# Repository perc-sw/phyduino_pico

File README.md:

# Phyduino Pico

## Description

This repository has all CAD files for the Phyduino Pico board used in the University of Toronto, Department of Physic, "[Introduction to Electronics course.](https://perc-sw.github.io/intro_to_electronics/)" 

This board is used to train graduate students first and foremost in surface mount hole solder techniques. As part of the training in the course they will as learn digital interfaces and digital IO design methods as well. This board is a fully function Arduino Uno style board using the Raspberry PI RP2040 microcontroller.

The CAD program used to design this board is [KiCAD](https://www.kicad.org/) which open source and free to use. The [Interactive Html BoM](https://github.com/openscopeproject/InteractiveHtmlBom) plugin was used to generate the interactive bill of materials html file.

## Files

- Gerber Files are located in the [fabrication folder](./fab)
- There is an [Interactive bill of materials html file](https://perc-sw.github.io/phyduino_pico/bom/ibom_student.html) that you can use to assist you in assembling the board. 
- PDF of [Schematic](./docs/pdf/board/phyduino_pico_schematic.pdf)
- PDF of PCB
    - [Top Layer](./docs/pdf/board/phyduino_pico_pcb_front.pdf)
    - [Inner Layer 1](./docs/pdf/board/phyduino_pico_pcb_inner1.pdf)
    - [Inner Layer 2](./docs/pdf/board/phyduino_pico_pcb_inner2.pdf)
    - [Bottom Layer](./docs/pdf/board/phyduino_pico_pcb_back.pdf)

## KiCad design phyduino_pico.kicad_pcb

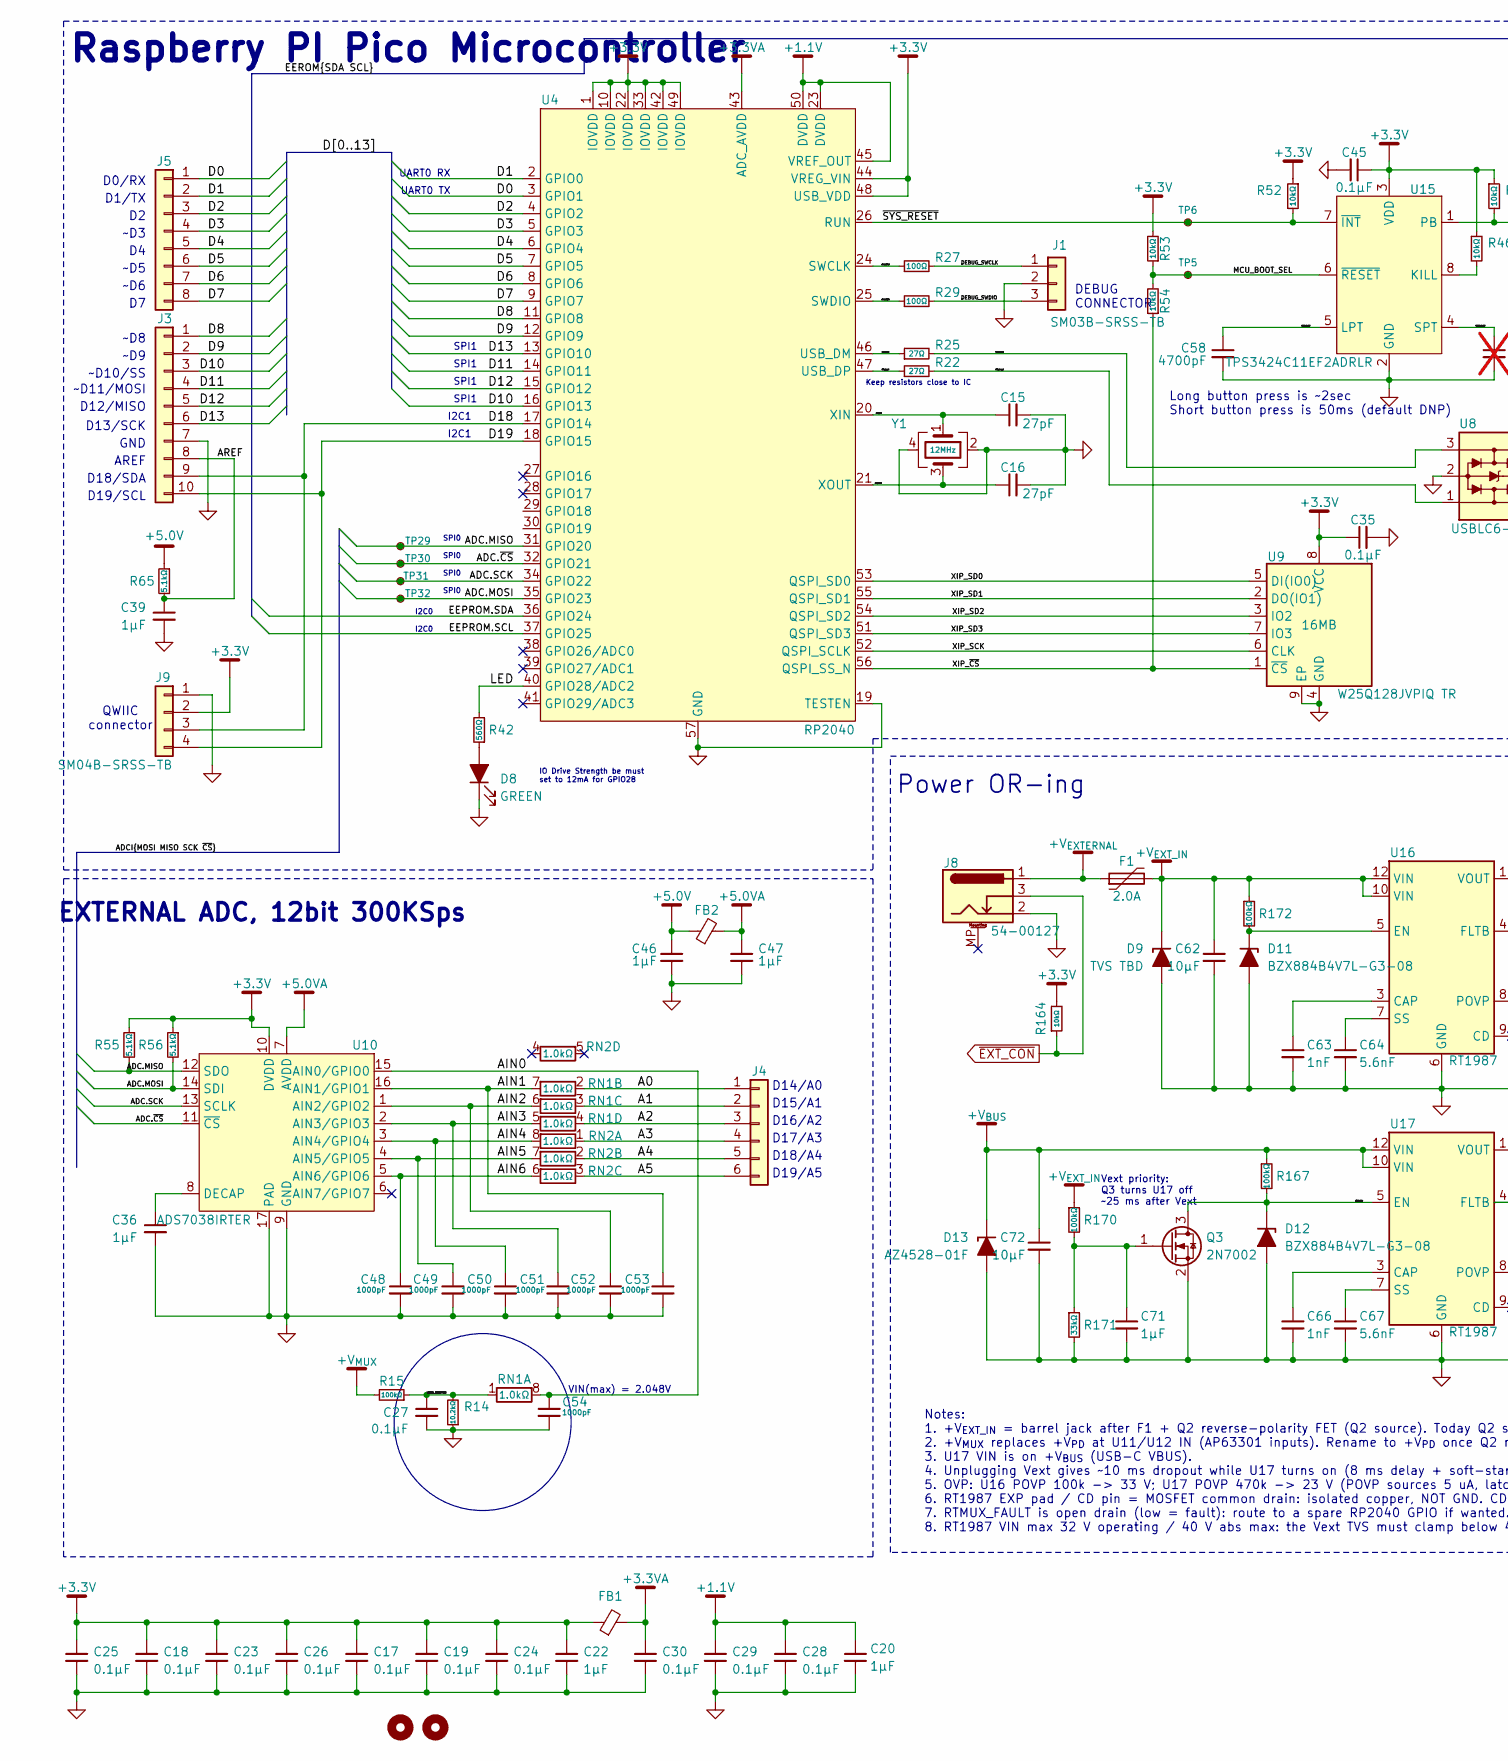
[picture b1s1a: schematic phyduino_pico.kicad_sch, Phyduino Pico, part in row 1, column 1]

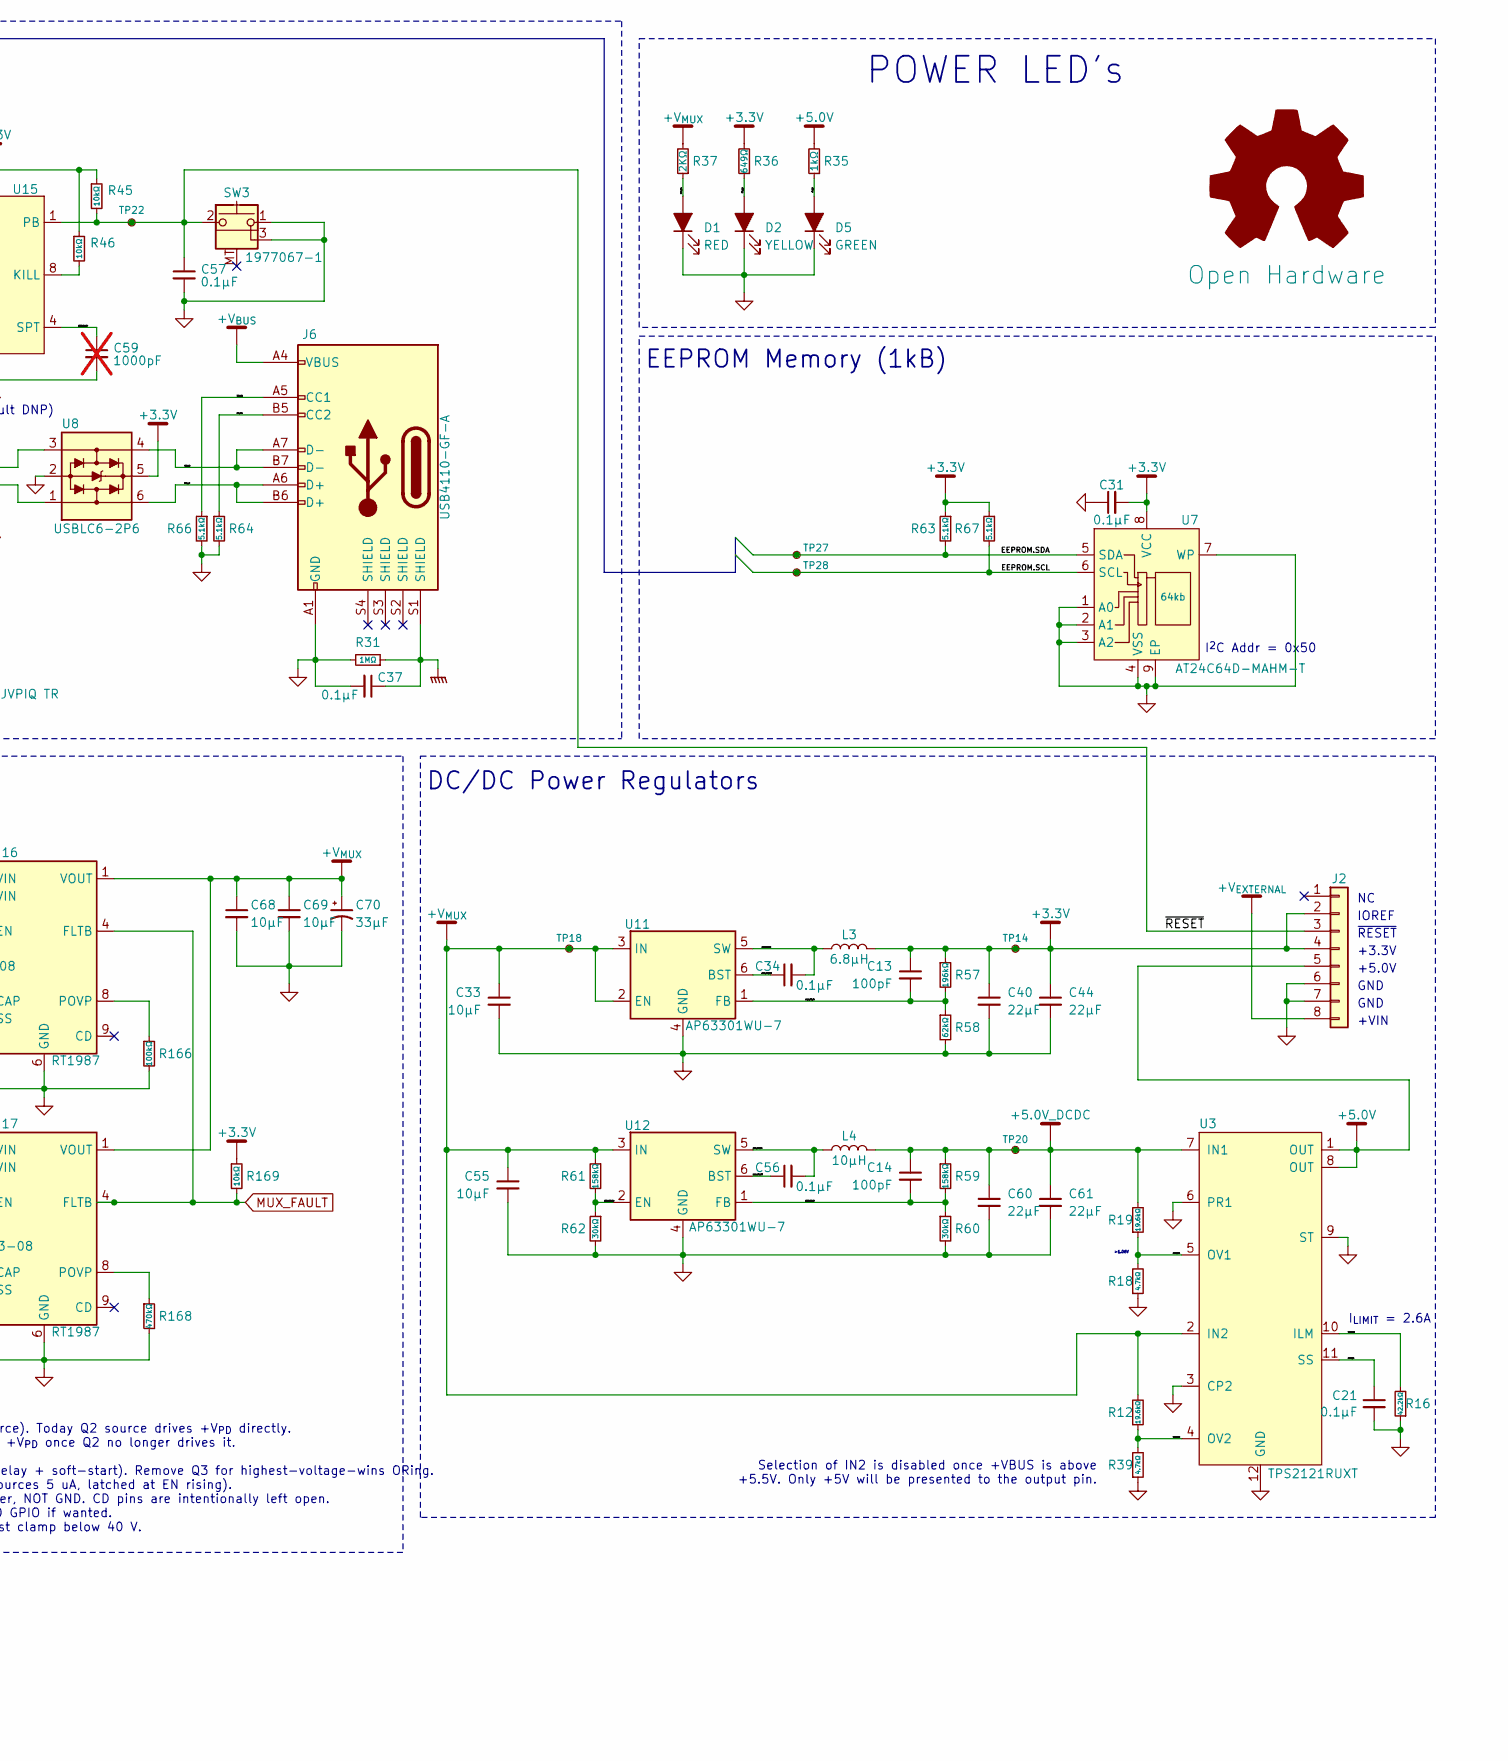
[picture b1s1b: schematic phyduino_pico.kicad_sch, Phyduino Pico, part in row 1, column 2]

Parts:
C13, C14: 100pF; C_0402_1005Metric; MOUSER_PN 187-CL05C101JB5NNNC; DIGIKEY_PN 1276-1025-1-ND
C15, C16: 27pF; C_0402_1005Metric
C17, C18, C19, C21, C23, C24, C25, C26, C27, C28, C29, C30, C35: 0.1µF; C_0402_1005Metric
C20, C22, C71: 1µF; C_0402_1005Metric
C31, C45, C57: 0.1µF; C_0402_1005Metric; Tolerance ±10%; MOUSER_PN 81-GCM155R71H104KE2J; LCSC_PN C85858
C33, C55: 10µF; C_0805_2012Metric_Pad1.18x1.45mm_HandSolder; MOUSER_PN 603-CC0805KKX59BB106; LCSC_PN C440198
C34, C56: 0.1µF; C_0805_2012Metric_Pad1.18x1.45mm_HandSolder; MOUSER_PN 187-CL21B104KBCNNNC; LCSC_PN C1711
C36, C46, C47: 1µF; C_0805_2012Metric_Pad1.18x1.45mm_HandSolder; Tolerance ±10%; MOUSER_PN 81-GCM21BR71H105KA3L; LCSC_PN C342759
C37: 0.1µF; C_0805_2012Metric_Pad1.18x1.45mm_HandSolder
C39: 1µF; C_0402_1005Metric; MOUSER_PN 187-CL05A105KO5NNNC; LCSC_PN C29266
C40, C44, C61: 22µF; C_1206_3216Metric_Pad1.33x1.80mm_HandSolder; Tolerance ±20%; MOUSER_PN 810-C3216X5R1E226M; DIGIKEY_PN 445-6000-1-ND
C48, C49, C50, C51, C52, C53, C54: 1000pF; C_0402_1005Metric; Tolerance ±5%; MOUSER_PN 81-GRM1555C1H102JA1D; LCSC_PN C76947
C58: 4700pF; C_0402_1005Metric; Tolerance ±5%; MOUSER_PN 81-GRM1555C1H472JE1D; LCSC_PN C1518204
C59: 1000pF; C_0402_1005Metric; Tolerance ±5%; MOUSER_PN 81-GRM1555C1H102JA1D; LCSC_PN C76947; not fitted
C60: 22µF; C_1206_3216Metric_Pad1.33x1.80mm_HandSolder; Tolerance ±20%; VOLTAGE 25V; MOUSER_PN 810-C3216X5R1E226M; DIGIKEY_PN 445-6000-1-ND
C62, C68, C69, C72: 10µF; C_0805_2012Metric_Pad1.18x1.45mm_HandSolder; MOUSER_PN 603-CC0805KKX59BB106; DIGIKEY_PN 4713-GMC21X5R106K50NTCT-ND
C63, C66: 1nF; C_0402_1005Metric
C64, C67: 5.6nF; C_0402_1005Metric
C70: 33µF; CP_Elec_6.3x7.7; DIGIKEY_PN P15464CT-ND
D1: RED; LED_0805_2012Metric_Pad1.15x1.40mm_HandSolder
D2: YELLOW; LED_0805_2012Metric_Pad1.15x1.40mm_HandSolder
D5: GREEN; LED_0805_2012Metric_Pad1.15x1.40mm_HandSolder
D8: GREEN; LED_0402_1005Metric
D9: TVS TBD; DFN1610P2E
D11, D12: BZX884B4V7L-G3-08; D_SOD-882; DIGIKEY_PN 112-BZX884B4V7L-G3-08CT-ND
D13: AZ4528-01F; DFN1610P2E; DIGIKEY_PN 4430-AZ4528-01F-ND
DRAW1: Open Hardware; OSHW-Logo2_9.8x8mm_SilkScreen
F1: 2.0A; Fuse_1206_3216Metric
FB1: BLM15AG221SH1D; L_0402_1005Metric
FB2: 1kΩ@100MHz; L_0805_2012Metric_Pad1.05x1.20mm_HandSolder; MOUSER_PN 875-HZ0805D102R-10; LCSC_PN C85835
H1, H3: MountingHole; MountingHole_3.2mm_M3
J1: SM03B-SRSS-TB; JST_SH_SM03B-SRSS-TB_1x03-1MP_P1.00mm_Horizontal
J2, J5: Conn_01x08; PinSocket_1x08_P2.54mm_Vertical
J3: Conn_01x10; PinSocket_1x10_P2.54mm_Vertical
J4: Conn_01x06; PinSocket_1x06_P2.54mm_Vertical
J6: USB4110-GF-A; GCT-USBC-GCT_USB4110
J8: 54-00127; TENSILITY_54-00127; DIGIKEY_PN 839-54-00127-ND
J9: SM04B-SRSS-TB; JST_SH_SM04B-SRSS-TB_1x04-1MP_P1.00mm_Horizontal; MOUSER_PN 306-SM04BSRSSTBLFSN; DIGIKEY_PN 455-SM04B-SRSS-TBCT-ND
L3: 6.8µH; L_Bourns_SRP4021HMCT; MOUSER_PN 652-SRP4021HMCT-6R8M; LCSC PN C47146736
L4: 10µH; L_Bourns_SRP4021HMCT; MOUSER_PN 652-SRP4021HMCT-100M; LCSC PN C47146732
Q3: 2N7002; SOT-23
R12, R19: 19.6kΩ; R_0402_1005Metric
R14: 10.2kΩ; R_0402_1005Metric
R15, R166, R167, R170, R172: 100kΩ; R_0402_1005Metric
R16: 42.2kΩ; R_0402_1005Metric
R18, R39: 4.7kΩ; R_0402_1005Metric
R22, R25: 27Ω; R_0402_1005Metric
R27, R29: 100Ω; R_0402_1005Metric
R31: 1MΩ; R_0805_2012Metric_Pad1.20x1.40mm_HandSolder
R35: 1kΩ; R_0805_2012Metric_Pad1.20x1.40mm_HandSolder
R36: 649Ω; R_0805_2012Metric_Pad1.20x1.40mm_HandSolder
R37: 2KΩ; R_0805_2012Metric_Pad1.20x1.40mm_HandSolder
R42: 560Ω; R_0402_1005Metric
R45, R46, R52, R53, R54, R164: 10kΩ; R_0402_1005Metric; MOUSER_PN 603-RC0402FR-0710KL; LCSC_PN C60490
R55, R56, R63, R65, R67: 5.1kΩ; R_0402_1005Metric; MOUSER_PN 603-RC0402FR-075K1L; LCSC_PN C105872
R57: 196kΩ; R_0402_1005Metric; MOUSER_PN 603-RC0402FR-07196KL; LCSC_PN C26996
R58: 62kΩ; R_0402_1005Metric; MOUSER_PN 603-RC0402FR-0762KL; LCSC_PN C2909375
R59, R61: 158kΩ; R_0402_1005Metric; MOUSER_PN 603-RC0402FR-07158KL; LCSC_PN C4014665
R60, R62: 30kΩ; R_0402_1005Metric; MOUSER_PN 603-RC0402FR-0730KL; LCSC_PN C138008
R64, R66: 5.1kΩ; R_0402_1005Metric; MOUSER_PN 603-RC0402FR-0762KL; LCSC_PN C2909375
R168: 470kΩ; R_0402_1005Metric
R169: 10kΩ; R_0402_1005Metric
R171: 33kΩ; R_0402_1005Metric
RN1, RN2: 1.0kΩ; RESCAV50P200X100X55-8N; MOUSER_PN 652-CAT10-102J4LF; DIGIKEY_PN CAT10-102J4LFCT-ND
SW3: 1977067-1; TE_1977067-1; LCSC PN C2972216
TP5, TP6, TP14, TP18, TP20, TP22, TP27, TP28, TP29, TP30, TP31, TP32: TestPoint_Small; TestPoint_SameSky_CPG-47-TH-B
U3: TPS2121RUXT; VQFN-HR-12
U4: RP2040; QFN-56-1EP_7x7mm_P0.4mm_EP3.2x3.2mm
U7: AT24C64D-MAHM-T; DFN-8-1EP_3x2mm_P0.5mm_EP1.3x1.4mm; LCSC_PN C2061553
U8: USBLC6-2P6; SOT-666
U9: W25Q128JVPIQ TR; WSON-8-1EP_6x5mm_P1.27mm_EP3.4x4.3mm
U10: ADS7038IRTER; QFN50P300X300X80-17N; MOUSER_PN 595-ADS7038IRTER; LCSC_PN C2871580
U11, U12: AP63301WU-7; TSOT-23-6_HandSoldering; MOUSER_PN 621-AP63301WU-7; DIGIKEY_PN 31-AP63301WU-7CT-ND
U15: TPS3424C11EF2ADRLR; SOT-5x3_DRL0008A_TEX; MOUSER_PN 595-S3424C11EF2ADRLR; DIGIKEY_PN 296-TPS3424C11EF2ADRLRCT-ND
U16, U17: RT1987; Richtek_VDFN-12T1L_3x3mm
Y1: H130B-12.000-18-3030-TR; Oscillator_SMD_Abracon_ASE-4Pin_3.2x2.5mm

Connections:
+1.1V: C20.1, C28.1, C29.1, U4.23 (DVDD), U4.45 (VREF_OUT), U4.50 (DVDD)
+3.3V: C13.1, C17.1, C18.1, C19.1, C22.1, C23.1, C24.1, C25.1, C26.1, C31.2, C35.1, C40.1, C44.1, C45.1, FB1.1, J2.2, J2.4, J9.2, L3.2, R36.2, R45.1, R46.1, R52.1, R53.2, R55.1, R56.1, R57.1, R63.1, R67.1, R164.2, R169.1, TP14.1 (1_1), U4.1 (IOVDD), U4.10 (IOVDD), U4.22 (IOVDD), U4.33 (IOVDD), U4.42 (IOVDD), U4.44 (VREG_VIN), U4.48 (USB_VDD), U4.49 (IOVDD), U7.8 (VCC), U8.5 (VBUS), U9.8 (VCC), U10.10 (DVDD), U15.3 (VDD)
+3.3VA: C30.1, FB1.2, U4.43 (ADC_AVDD)
+5.0V: C46.1, FB2.1, J2.5, R35.2, R65.1, U3.1 (OUT), U3.8 (OUT)
+5.0VA: C47.1, FB2.2, U10.7 (AVDD)
+5.0V_DCDC: C14.1, C60.1, C61.1, L4.2, R19.2, R59.1, TP20.1 (1_1), U3.7 (IN1)
+V_{BUS}: C72.1, D13.1 (K), J6.A4 (VBUS), J6.A9 (VBUS), J6.B4 (VBUS), J6.B9 (VBUS), R167.1, U17.10 (VIN), U17.12 (VIN)
+V_{EXTERNAL}: F1.1, J2.8, J8.1
+V_{EXT_IN}: C62.1, D9.1 (K), F1.2, R170.1, R172.1, U16.10 (VIN), U16.12 (VIN)
+V_{MUX}: C33.1, C55.1, C68.1, C69.1, C70.1, R12.2, R15.2, R37.2, R61.1, TP18.1 (1_1), U3.2 (IN2), U11.2 (EN), U11.3 (IN), U12.3 (IN), U16.1 (VOUT), U17.1 (VOUT)
/3V3_LED: D2.2 (A), R36.1
/5V_LED: D5.2 (A), R35.1
/A0: J4.1, RN1.2 (R2.1)
/A1: J4.2, RN1.3 (R3.1)
/A2: J4.3, RN1.4 (R4.1)
/A3: J4.4, RN2.1 (R1.1)
/A4: J4.5, RN2.2 (R2.1)
/A5: J4.6, RN2.3 (R3.1)
/ADC.MISO: R55.2, TP29.1 (1_1), U4.31 (GPIO20), U10.12 (SDO)
/ADC.MOSI: R56.2, TP32.1 (1_1), U4.35 (GPIO23), U10.14 (SDI)
/ADC.SCK: TP31.1 (1_1), U4.34 (GPIO22), U10.13 (SCLK)
/ADC.~CS: TP30.1 (1_1), U4.32 (GPIO21), U10.11 (~CS)
/AIN0: C54.1, RN1.8 (R1.2), U10.15 (AIN0/GPIO0)
/AIN1: C53.1, RN1.7 (R2.2), U10.16 (AIN1/GPIO1)
/AIN2: C52.1, RN1.6 (R3.2), U10.1 (AIN2/GPIO2)
/AIN3: C51.1, RN1.5 (R4.2), U10.2 (AIN3/GPIO3)
/AIN4: C50.1, RN2.8 (R1.2), U10.3 (AIN4/GPIO4)
/AIN5: C49.1, RN2.7 (R2.2), U10.4 (AIN5/GPIO5)
/AIN6: C48.1, RN2.6 (R3.2), U10.5 (AIN6/GPIO6)
/AREF: C39.1, J3.8, R65.2
/BOOT_LP_CAP: C58.1, U15.5 (LPT)
/CPU_XIN: C15.1, U4.20 (XIN), Y1.1
/CPU_XOUT: C16.1, U4.21 (XOUT), Y1.3
/D0: J5.1, U4.3 (GPIO1)
/D1: J5.2, U4.2 (GPIO0)
/D2: J5.3, U4.4 (GPIO2)
/D3: J5.4, U4.5 (GPIO3)
/D4: J5.5, U4.6 (GPIO4)
/D5: J5.6, U4.7 (GPIO5)
/D6: J5.7, U4.8 (GPIO6)
/D7: J5.8, U4.9 (GPIO7)
/D8: J3.1, U4.11 (GPIO8)
/D9: J3.2, U4.12 (GPIO9)
/D10: J3.3, U4.16 (GPIO13)
/D11: J3.4, U4.14 (GPIO11)
/D12: J3.5, U4.15 (GPIO12)
/D13: J3.6, U4.13 (GPIO10)
/D18: J3.9, J9.3, U4.17 (GPIO14)
/D19: J3.10, J9.4, U4.18 (GPIO15)
/DCDC_3V3_BST: C34.1, U11.6 (BST)
/DCDC_3V3_FB: C13.2, R57.2, R58.1, U11.1 (FB)
/DCDC_3V3_SW: C34.2, L3.1, U11.5 (SW)
/DCDC_5V0_BST: C56.1, U12.6 (BST)
/DCDC_5V0_ENA: R61.2, R62.1, U12.2 (EN)
/DCDC_5V0_FB: C14.2, R59.2, R60.1, U12.1 (FB)
/DCDC_5V0_SW: C56.2, L4.1, U12.5 (SW)
/DEBUG_SWCLK: J1.1, R27.2
/DEBUG_SWDIO: J1.3, R29.2
/EEPROM.SCL: R67.2, TP28.1 (1_1), U4.37 (GPIO25), U7.6 (SCL)
/EEPROM.SDA: R63.2, TP27.1 (1_1), U4.36 (GPIO24), U7.5 (SDA)
/LED: R42.2, U4.40 (GPIO28/ADC2)
/MCU_BOOT_SEL: R53.1, R54.2, TP5.1 (1_1), U15.6 (~RESET)
/MCU_SWCLK: R27.1, U4.24 (SWCLK)
/MCU_SWDIO: R29.1, U4.25 (SWDIO)
/PMUX_LIM: R16.2, U3.10 (ILM)
/PMUX_OV1: R18.2, R19.1, U3.5 (OV1)
/PMUX_OV2: R12.1, R39.2, U3.4 (OV2)
/PMUX_SS: C21.1, U3.11 (SS)
/RESET_SP_CAP: C59.1, U15.4 (SPT)
/RTMUX_EN2: D12.1 (K), Q3.3 (D), R167.2, U17.5 (EN)
/USB_CC1: J6.A5 (CC1), R66.1
/USB_CC2: J6.B5 (CC2), R64.1
/USB_D_N: J6.A7 (D-), J6.B7 (D-), U8.4 (I/O2)
/USB_D_P: J6.A6 (D+), J6.B6 (D+), U8.6 (I/O1)
/USB_R_D_N: R25.1, U4.46 (USB_DM)
/USB_R_D_P: R22.1, U4.47 (USB_DP)
/USB_SP_D_N: R22.2, U8.1 (I/O1)
/USB_SP_D_P: R25.2, U8.3 (I/O2)
/VBUS_LED: D1.2 (A), R37.1
/VBUS_MONITOR: C27.1, R14.2, R15.1, RN1.1 (R1.1)
/XIP_SCK: U4.52 (QSPI_SCLK), U9.6 (CLK)
/XIP_SD0: U4.53 (QSPI_SD0), U9.5 (DI(IO0))
/XIP_SD1: U4.55 (QSPI_SD1), U9.2 (DO(IO1))
/XIP_SD2: U4.54 (QSPI_SD2), U9.3 (IO2)
/XIP_SD3: U4.51 (QSPI_SD3), U9.7 (IO3)
/XIP_~CS: R54.1, U4.56 (QSPI_SS_N), U9.1 (~CS)
/~RESET: C57.1, J2.3, R45.2, SW3.2, TP22.1 (1_1), U15.1 (PB)
/~SYS_RESET: R52.2, TP6.1 (1_1), U4.26 (RUN), U15.7 (~INT)
GND: C15.2, C16.2, C17.2, C18.2, C19.2, C20.2, C21.2, C22.2, C23.2, C24.2, C25.2, C26.2, C27.2, C28.2, C29.2, C30.2, C31.1, C33.2, C35.2, C36.2, C37.2, C39.2, C40.2, C44.2, C45.2, C46.2, C47.2, C48.2, C49.2, C50.2, C51.2, C52.2, C53.2, C54.2, C55.2, C57.2, C58.2, C59.2, C60.2, C61.2, C62.2, C63.2, C64.2, C66.2, C67.2, C68.2, C69.2, C70.2, C71.2, C72.2, D1.1 (K), D2.1 (K), D5.1 (K), D8.1 (K), D9.2 (A), D11.2 (A), D12.2 (A), D13.2 (A), J1.2, J2.6, J2.7, J3.7, J6.A1 (GND), J6.A12 (GND), J6.B1 (GND), J6.B12 (GND), J8.2, J9.1, Q3.2 (S), R14.1, R16.1, R18.1, R31.2, R39.1, R58.2, R60.2, R62.2, R64.2, R66.2, R166.2, R168.2, R171.2, SW3.1, SW3.3 (1), U3.3 (CP2), U3.6 (PR1), U3.9 (ST), U3.12 (GND), U4.19 (TESTEN), U4.57 (GND), U7.1 (A0), U7.2 (A1), U7.3 (A2), U7.4 (VSS), U7.7 (WP), U7.9 (EP), U8.2 (GND), U9.4 (GND), U9.9 (EP), U10.9 (GND), U10.17 (PAD), U11.4 (GND), U12.4 (GND), U15.2 (GND), U16.6 (GND), U17.6 (GND), Y1.2, Y1.4
GNDPWR: C37.1, J6.S1 (SHIELD), R31.1
MUX_FAULT: R169.2, U16.4 (FLTB), U17.4 (FLTB)
unnamed: D8.2 (A), R42.1
unnamed: D11.1 (K), R172.2, U16.5 (EN)
unnamed: C71.1, Q3.1 (G), R170.2, R171.1
unnamed: C36.1, U10.8 (DECAP)
unnamed: R46.2, U15.8 (KILL)
unnamed: C63.1, U16.3 (CAP)
unnamed: R166.1, U16.8 (POVP)
unnamed: C64.1, U16.7 (SS)
unnamed: C66.1, U17.3 (CAP)
unnamed: R168.1, U17.8 (POVP)
unnamed: C67.1, U17.7 (SS)
~EXT_CON: J8.3, R164.1

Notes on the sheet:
~D11/MOSI
~D8
AREF
VIN(max) = 2.048V
D19/A5
SPI0
+3.3V
Long button press is ~2sec Short button press is 50ms (default DNP)
D17/A3
EXTERNAL ADC, 12bit 300KSps
Notes: 1. +V_{EXT_IN} = barrel jack after F1 + Q2 reverse-polarity FET (Q2 source). Today Q2 source drives +V_{PD} directly. 2. +V_{MUX} replaces +V_{PD} at U11/U12 IN (AP63301 inputs). Rename to +V_{PD} once Q2 no longer drives it. 3. U17 VIN is on +V_{BUS} (USB-C VBUS). 4. Unplugging Vext gives ~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
~{RESET}
D13/SCK
IOREF
DC/DC Power Regulators
~D5
D12/MISO
Selection of IN2 is disabled once +VBUS is above +5.5V. Only +5V will be presented to the output pin.
D15/A1
QWIIC connector
I2C0
Raspberry PI Pico Microcontroller
EEPROM Memory (1kB)
>1.06V
GND
UART0 RX
IO Drive Strength be must set to 12mA for GPIO28
UART0 TX
DEBUG CONNECTOR
~D6
I2C1
SPI1
D19/SCL
~D3
I_{LIMIT} = 2.6A
~D10/SS
+5.0V
~D9
+VIN
D1/TX

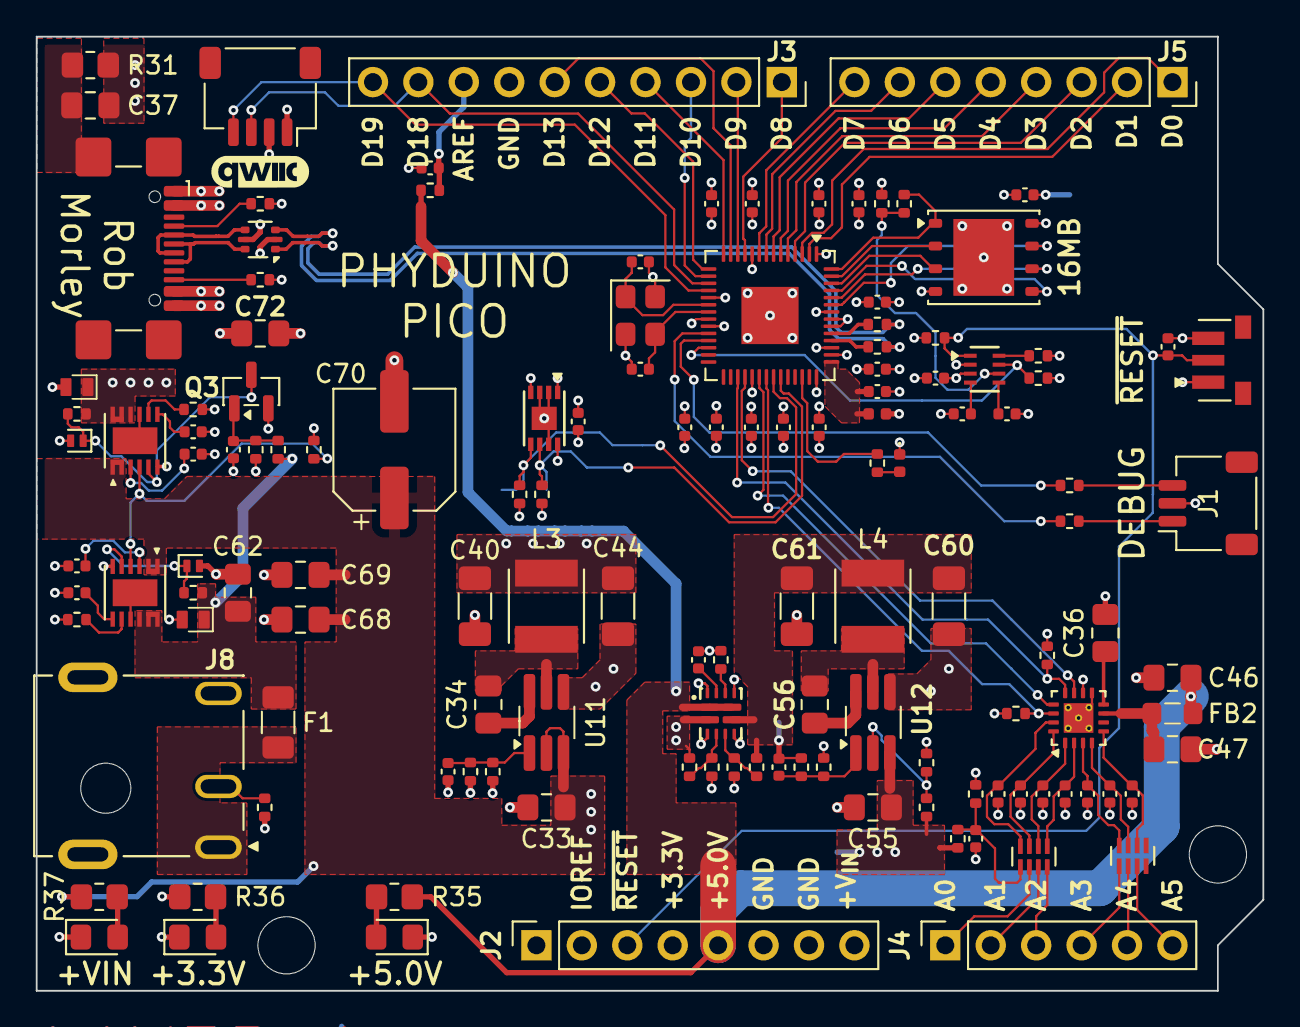
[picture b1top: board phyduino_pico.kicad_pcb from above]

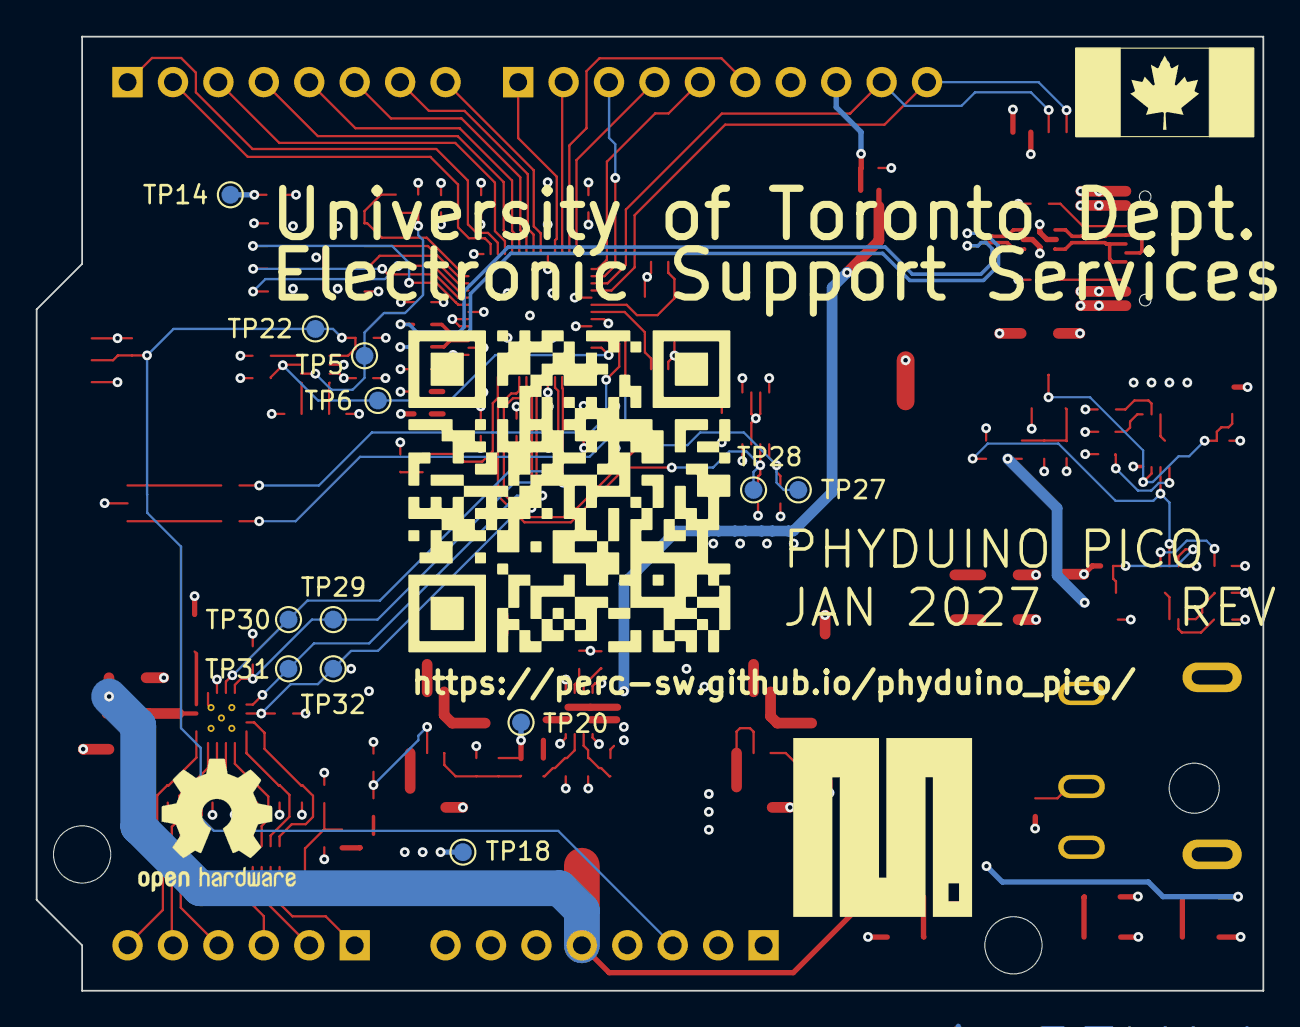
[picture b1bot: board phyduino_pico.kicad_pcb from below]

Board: 4 copper layers, 68.6 x 53.3 mm, 148 parts (13 on the bottom side), 103 nets.

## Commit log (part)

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2026-05-04 Rev E files added
2026-05-05 Added board datasheets to repository.
2026-05-05 Updated 3D model links and change PCB notes for better printing.
2026-05-30 Orginized directory structure for GitHub pages. Updated documentation.
2026-05-30 Minor change to iBoM
2026-05-30 Read me update.
2026-05-30 PCB fabrication output update.
2026-05-30 added .zip file ignore to fab folder.
2026-05-30 Creation of GitHub docs index.html
2026-05-30 Update to index.html icon.
2026-05-31 index.html title up date.
2026-05-31 Added tab icon to ibom_student.html
2026-05-31 Change GitHub docs layout.
2026-06-01 Modified .gitignore
2026-06-01 Added mobile capability to GitHub pages
2026-06-02 Changed page logo to PLRS logo.
2026-06-02 Fixed PLRS logo.
2026-06-03 Graphics fix to PLRS logo
2026-06-03 Header logo update.
2026-06-09 Add pin-out diagram and updated ibom.
2026-06-09 Updated pin-out doc
2026-06-09 Corrected ref designator error
